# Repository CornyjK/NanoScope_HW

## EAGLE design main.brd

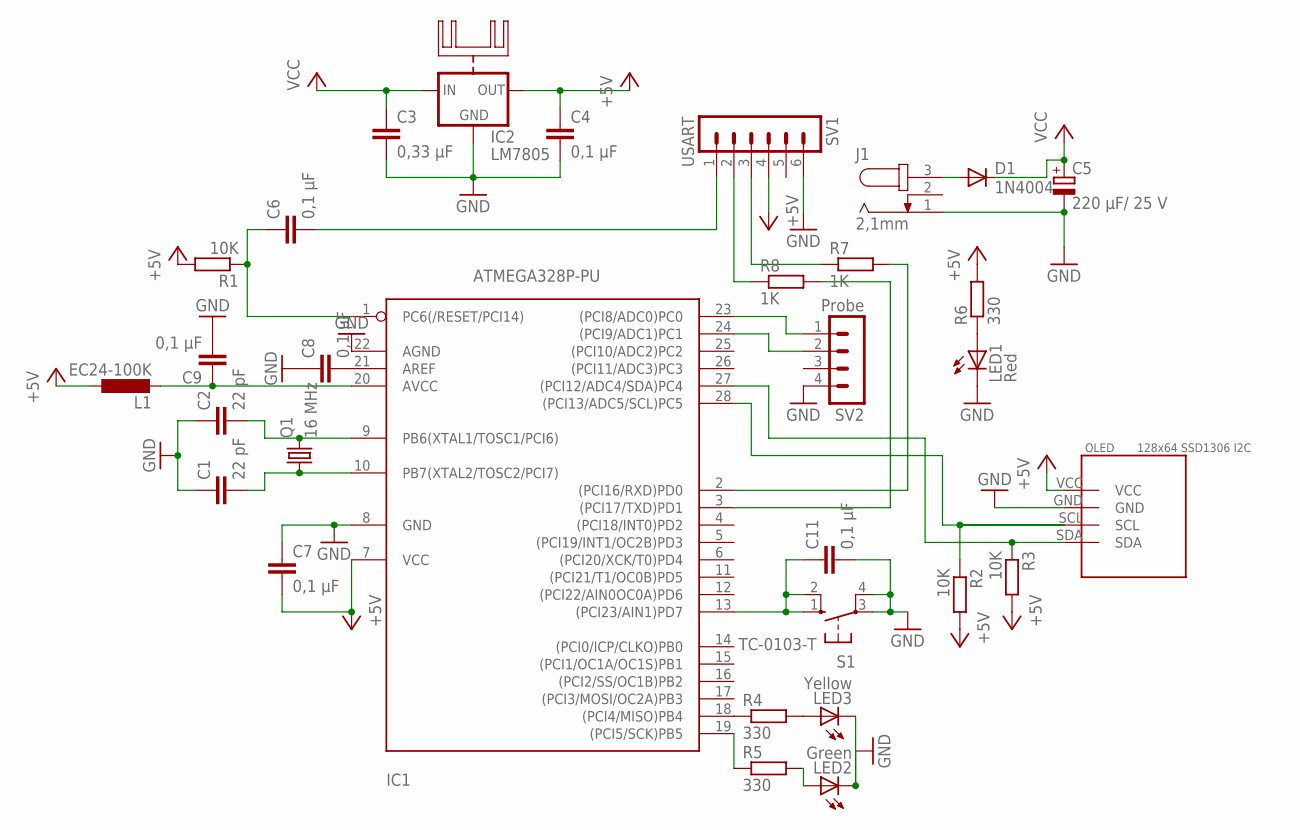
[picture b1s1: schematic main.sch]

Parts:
C1, C2: 22 pF; C025-025X050
C3: 0,33 μF; C050-025X075
C4, C6, C7, C8, C9, C11: 0,1 μF; C050-025X075
C5: 220 μF/ 25 V; E5-8,5
D1: 1N4004; DO41-10
IC1: ATMEGA328P-PU; DIL28-3
IC2: LM7805; 78XXH
J1: 2,1mm; SPC4077
L1: EC24-100K; 0207/12
LED1: Red; LED5MM
LED2: Green; LED5MM
LED3: Yellow; LED5MM
OLED: 128x64 SSD1306 I2C; OLED_0.96_I2C
Q1: 16 MHz; HC49/S
R1, R2, R3: 10K; 0207/7
R4, R5, R6: 330; 0207/7
R7, R8: 1K; 0207/7
S1: TC-0103-T; B3F-10XX
SV1: USART; MA06-1
SV2: Probe; MA04-1

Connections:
+5V: C4.1, C7.2, IC1.7 (VCC), IC2.OUT, L1.1, OLED.VCC, R1.2, R2.2, R3.2, R6.2, SV1.4
BTN: C11.1, IC1.13 ((PCI23/AIN1)PD7), S1.1 (S), S1.2 (S1)
GND: C1.1, C2.1, C3.2, C4.2, C5.-, C7.1, C8.1, C9.2, C11.2, IC1.8 (GND), IC1.22 (AGND), IC2.GND, J1.1, LED1.K (C), LED2.K (C), LED3.K (C), OLED.GND, S1.3, S1.4 (P1), SV1.6, SV2.4
IJVCC: D1.A, J1.3
unnamed: C1.2, IC1.10 (PB7(XTAL2/TOSC2/PCI7)), Q1.1
unnamed: C2.2, IC1.9 (PB6(XTAL1/TOSC1/PCI6)), Q1.2
unnamed: IC1.27 ((PCI12/ADC4/SDA)PC4), OLED.SDA, R3.1
unnamed: C6.1, IC1.1 (PC6(/RESET/PCI14)), R1.1
unnamed: C6.2, SV1.1
unnamed: IC1.2 ((PCI16/RXD)PD0), R7.2
unnamed: IC1.3 ((PCI17/TXD)PD1), R8.2
unnamed: IC1.23 ((PCI8/ADC0)PC0), SV2.1
unnamed: IC1.24 ((PCI9/ADC1)PC1), SV2.2
unnamed: C8.2, IC1.21 (AREF)
unnamed: IC1.18 ((PCI4/MISO)PB4), R4.1
unnamed: IC1.19 ((PCI5/SCK)PB5), R5.1
unnamed: LED3.A, R4.2
unnamed: C9.1, IC1.20 (AVCC), L1.2
unnamed: LED2.A, R5.2
unnamed: LED1.A, R6.1
unnamed: R8.1, SV1.2
unnamed: R7.1, SV1.3
SCL: IC1.28 ((PCI13/ADC5/SCL)PC5), OLED.SCL, R2.1
VCC: C3.1, C5.+, D1.C, IC2.IN

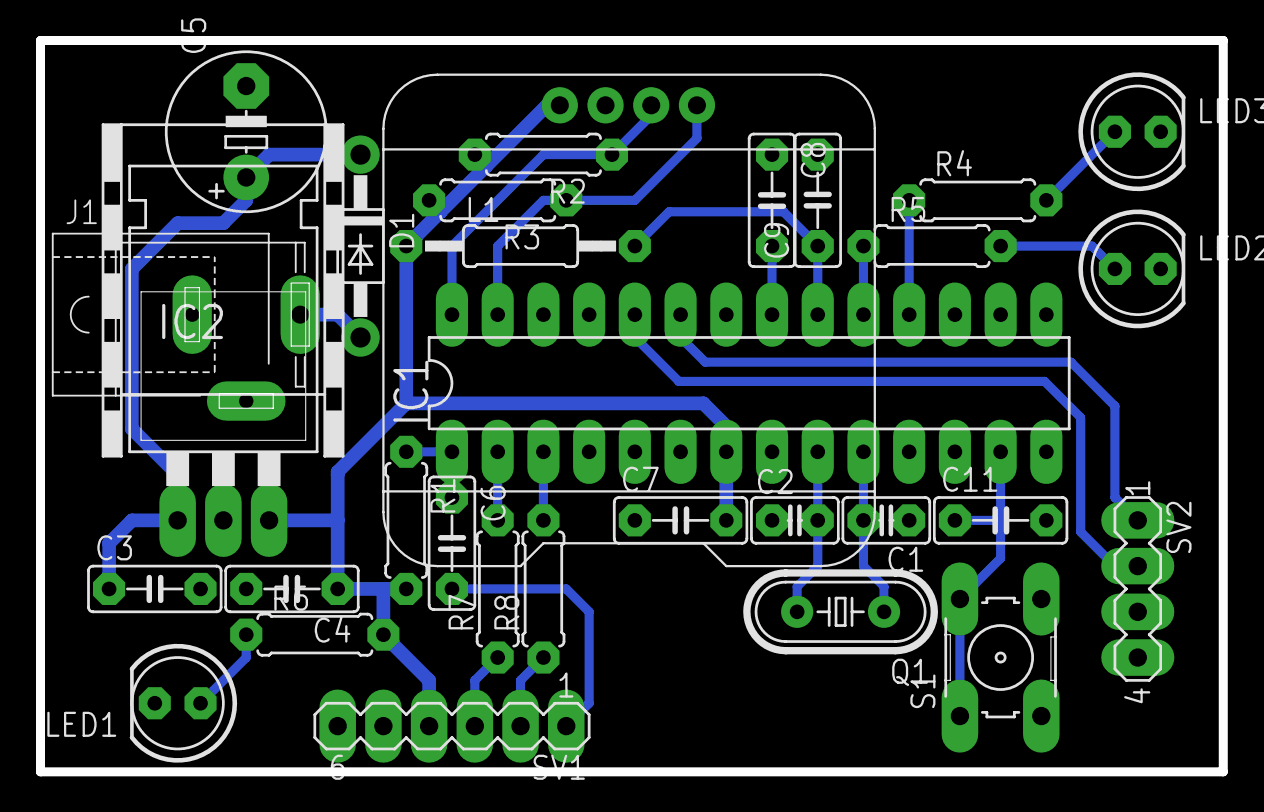
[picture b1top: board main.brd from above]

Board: 2 copper layers, 65.7 x 40.6 mm, 31 parts (0 on the bottom side), 24 nets.

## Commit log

2017-05-17 Nahrání 1. revize
2017-05-18 Minor fixes
2017-05-19 Opravy
2017-05-20 Revize 0.0.1
2017-06-02 Opravy na celorepublikové kolo
